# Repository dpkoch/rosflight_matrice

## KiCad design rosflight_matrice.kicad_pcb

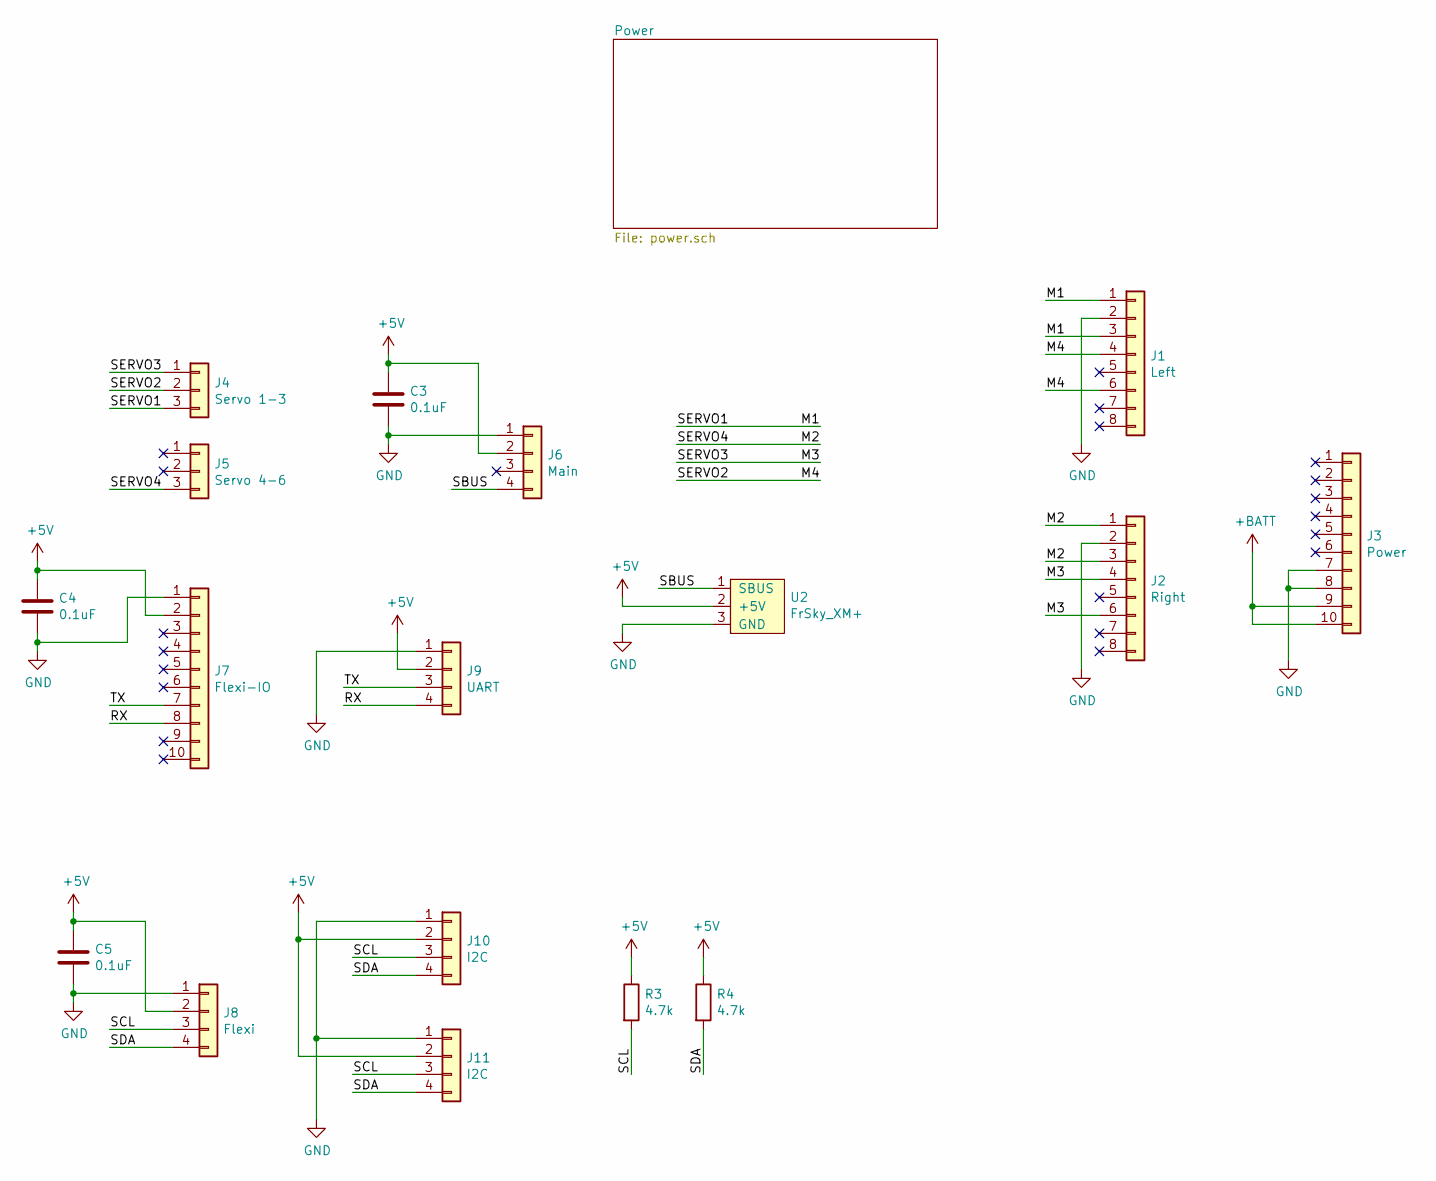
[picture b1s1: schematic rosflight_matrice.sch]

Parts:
C3, C4, C5: 0.1uF; C_0805_2012Metric_Pad1.15x1.40mm_HandSolder
J1: Left; JST_GH_SM08B-GHS-TB_1x08-1MP_P1.25mm_Horizontal
J2: Right; JST_GH_SM08B-GHS-TB_1x08-1MP_P1.25mm_Horizontal
J3: Power; JST_GH_SM10B-GHS-TB_1x10-1MP_P1.25mm_Horizontal
J4: Servo 1-3; Molex_KK-7478_1x03_P2.54mm_Horizontal
J5: Servo 4-6; Molex_KK-7478_1x03_P2.54mm_Horizontal
J6: Main; JST_SH_SM04B-SRSS-TB_1x04-1MP_P1.00mm_Horizontal
J7: Flexi-IO; JST_SH_SM10B-SRSS-TB_1x10-1MP_P1.00mm_Horizontal
J8: Flexi; JST_SH_SM04B-SRSS-TB_1x04-1MP_P1.00mm_Horizontal
J9: UART; JST_GH_SM04B-GHS-TB_1x04-1MP_P1.25mm_Horizontal
J10, J11: I2C; JST_GH_SM04B-GHS-TB_1x04-1MP_P1.25mm_Horizontal
R3, R4: 4.7k; R_0603_1608Metric_Pad1.05x0.95mm_HandSolder
U2: FrSky_XM+

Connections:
+5V: C3.1, C4.1, C5.1, J6.2, J7.2, J8.2, J9.2, J10.2, J11.2, R3.1, R4.1, U2.2 (+5V); also elsewhere on the board
+BATT: J3.9, J3.10; also elsewhere on the board
/M1: J1.1, J1.3, J4.3
/M2: J2.1, J2.3, J5.3
/M3: J2.4, J2.6, J4.1
/M4: J1.4, J1.6, J4.2
/RX: J7.8, J9.4
/SBUS: J6.4, U2.1 (SBUS)
/SCL: J8.3, J10.3, J11.3, R3.2
/SDA: J8.4, J10.4, J11.4, R4.2
/TX: J7.7, J9.3
GND: C3.2, C4.2, C5.2, J1.2, J2.2, J3.7, J3.8, J6.1, J7.1, J8.1, J9.1, J10.1, J11.1, U2.3 (GND); also elsewhere on the board

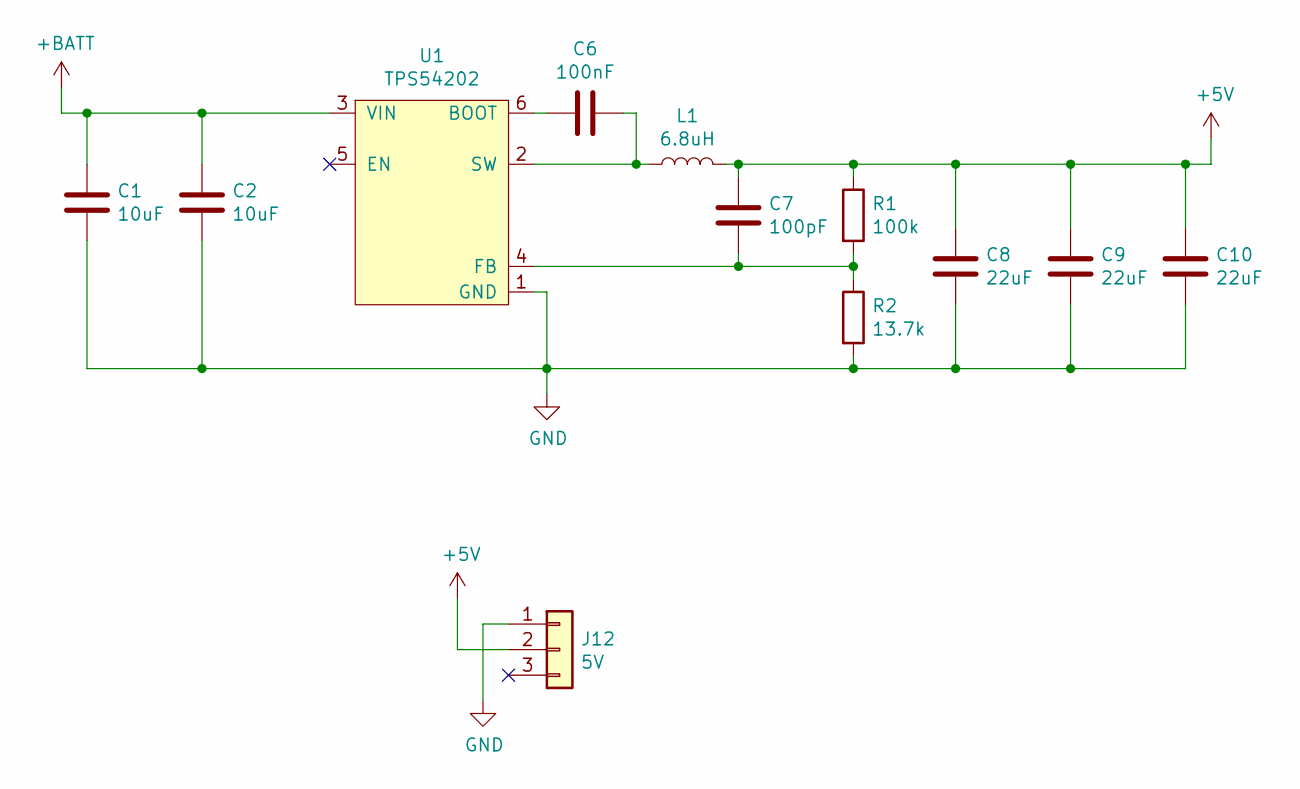
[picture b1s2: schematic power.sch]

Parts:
C1, C2: 10uF; C_1210_3225Metric_Pad1.42x2.65mm_HandSolder
C6: 100nF; C_0805_2012Metric_Pad1.15x1.40mm_HandSolder
C7: 100pF; C_0805_2012Metric_Pad1.15x1.40mm_HandSolder
C8, C9, C10: 22uF; C_1210_3225Metric_Pad1.42x2.65mm_HandSolder
J12: 5V; PinHeader_1x03_P2.54mm_Horizontal
L1: 6.8uH; SRN6045_HandSolder
R1: 100k; R_0805_2012Metric_Pad1.15x1.40mm_HandSolder
R2: 13.7k; R_0805_2012Metric_Pad1.15x1.40mm_HandSolder
U1: TPS54202; SOT-23-6_Handsoldering

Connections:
+5V: C7.1, C8.1, C9.1, C10.1, J12.2, L1.2, R1.1; also elsewhere on the board
+BATT: C1.1, C2.1, U1.3 (VIN); also elsewhere on the board
GND: C1.2, C2.2, C8.2, C9.2, C10.2, J12.1, R2.2, U1.1 (GND); also elsewhere on the board
unnamed: C6.1, L1.1, U1.2 (SW)
unnamed: C6.2, U1.6 (BOOT)
unnamed: C7.2, R1.2, R2.1, U1.4 (FB)

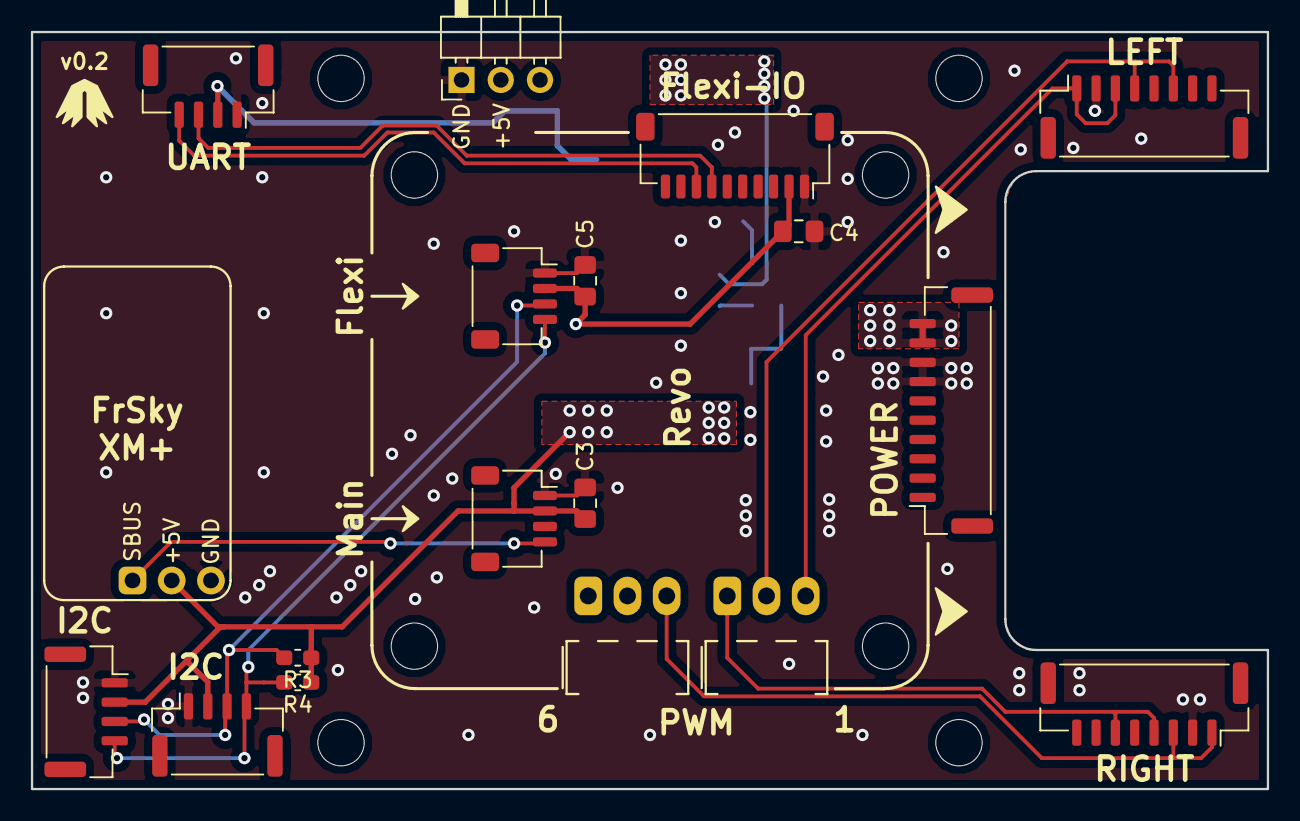
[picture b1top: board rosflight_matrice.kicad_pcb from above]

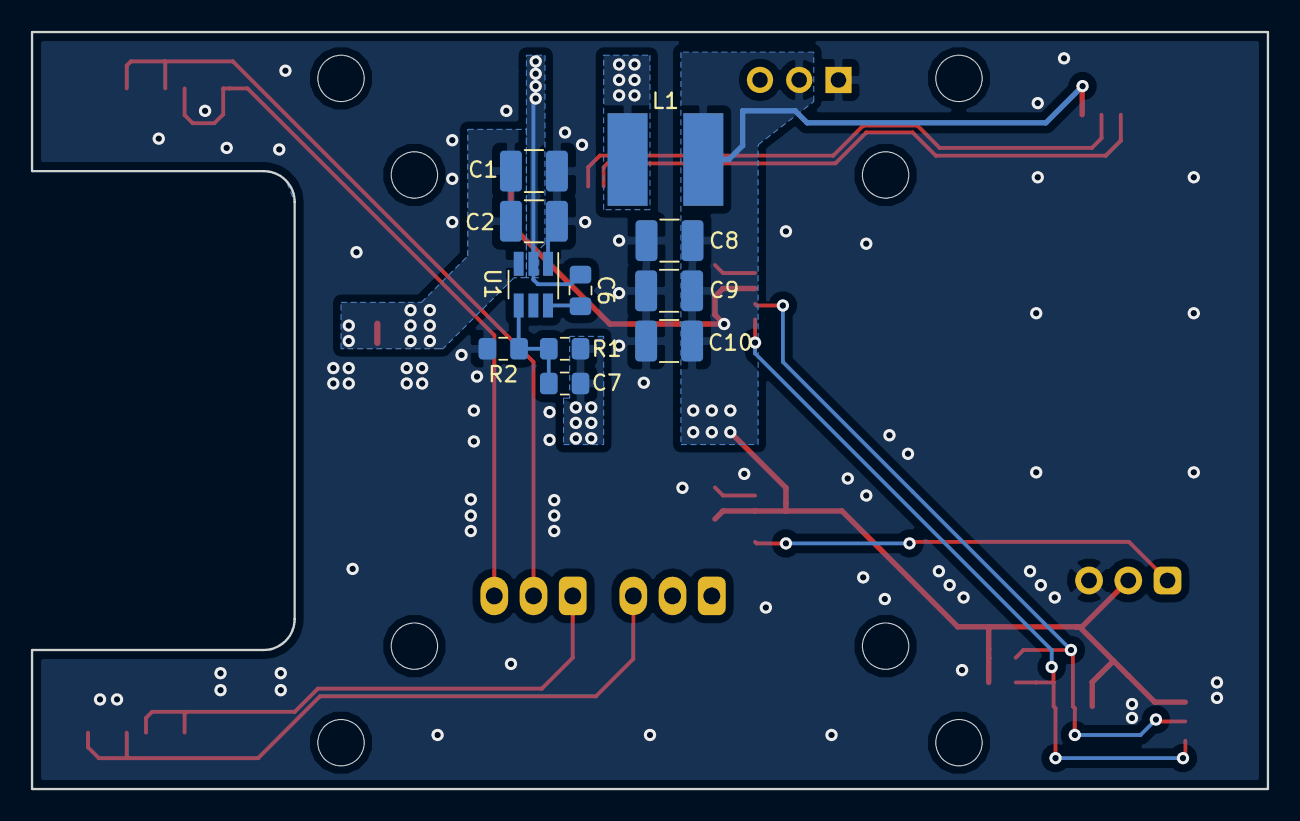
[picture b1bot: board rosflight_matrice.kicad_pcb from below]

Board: 2 copper layers, 80.0 x 49.0 mm, 29 parts (11 on the bottom side), 15 nets.

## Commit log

2019-05-23 v0.1
2019-10-28 New switching voltage regulator and updated layout
